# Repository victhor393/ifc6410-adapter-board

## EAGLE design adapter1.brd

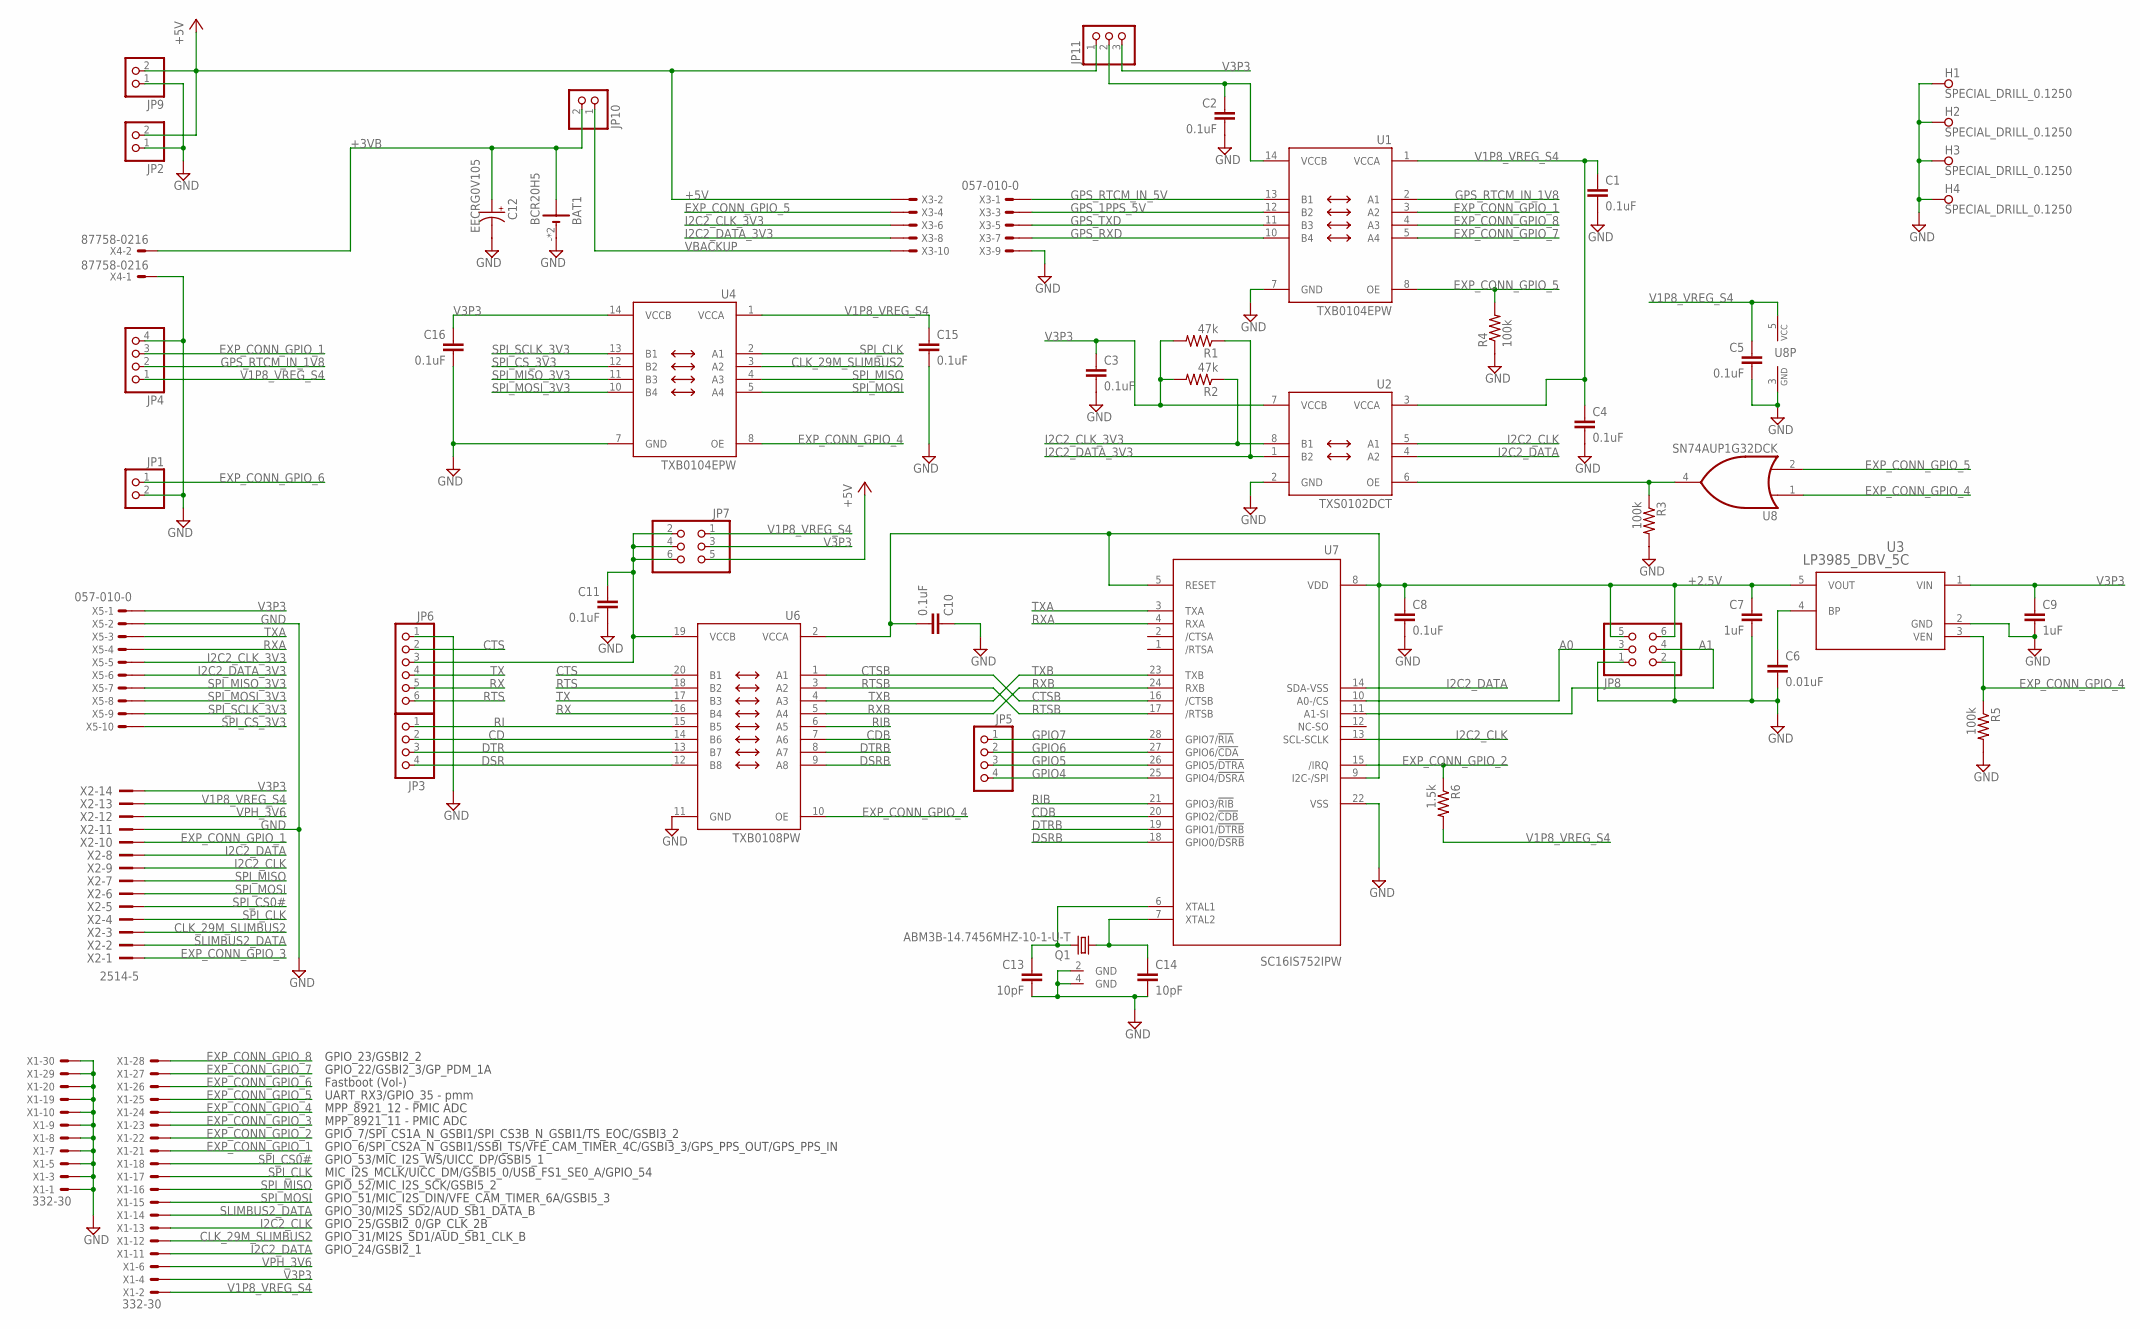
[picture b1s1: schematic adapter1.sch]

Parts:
BAT1: BCR20H5; BCR20H5_1066
C1, C2, C3, C4, C5, C8, C10, C11, C15, C16: 0.1uF; C0603
C6: 0.01uF; C0603
C7, C9: 1uF; C0603
C12: EECRG0V105; EB20D
C13, C14: 10pF; C0603
H1, H2, H3, H4: SPECIAL_DRILL_0.1250; PAD_0.1250
JP1, JP2, JP9: PINHD-1X2/90; 1X02/90
JP3, JP4, JP5: PINHD-1X4/90; 1X04/90
JP6: PINHD-1X6/90; 1X06/90
JP7: PINHD-2X3/90; 2X03/90
JP8: PINHD-2X3; 2X03
JP10: PINHD-1X2; 1X02
JP11: PINHD-1X3; 1X03
Q1: ABM3B-14.7456MHZ-10-1-U-T; ABM3B
R1, R2: 47k; R0603
R3, R4, R5: 100k; R0603
R6: 1.5k; R0603
U1, U4: TXB0104EPW; PW_R-PDSO-G14
U2: TXS0102DCT; DCT_R-PDSO-G8
U3: LP3985_DBV_5C; MF05A-M
U6: TXB0108PW; PW_R-PDSO-G20
U7: SC16IS752IPW; SSOP28
U8: SN74AUP1G32DCK; SC70-5
X1: 332-30
X2: 2514-5; PAK100/2500-5-14
X3, X5: 057-010-0
X4: 87758-0216

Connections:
+2.5V: C7.1, C8.1, C10.2, JP8.5, JP8.6, U3.5 (VOUT), U6.2 (VCCA), U7.5 (RESET), U7.8 (VDD), U7.9 (I2C-/SPI)
+3VB: BAT1.+, BAT1.+1 (+), C12.+, JP10.2, X4.2
+5V: JP2.2, JP7.5, JP9.2, JP11.1, X3.2
A0: JP8.3, U7.10 (A0-/CS)
A1: JP8.4, U7.11 (A1-SI)
CD: JP3.2, U6.14 (B6)
CDB: U6.7 (A6), U7.20 (GPIO2/!CDB)
CLK_29M_SLIMBUS2: U4.3 (A2), X1.12, X2.3
CTS: JP6.2, U6.20 (B1)
CTSB: U6.1 (A1), U7.16 (/CTSB)
DSR: JP3.4, U6.12 (B8)
DSRB: U6.9 (A8), U7.18 (GPIO0/!DSRB)
DTR: JP3.3, U6.13 (B7)
DTRB: U6.8 (A7), U7.19 (GPIO1/!DTRB)
EXP_CONN_GPIO_1: JP4.3, U1.3 (A2), X1.21, X2.10
EXP_CONN_GPIO_2: R6.1, U7.15 (/IRQ), X1.22
EXP_CONN_GPIO_3: X1.23, X2.1
EXP_CONN_GPIO_4: R5.1, U3.3 (VEN), U4.8 (OE), U6.10 (OE), U8.1 (I0), X1.24
EXP_CONN_GPIO_5: R4.2, U1.8 (OE), U8.2 (I1), X1.25, X3.4
EXP_CONN_GPIO_6: JP1.1, X1.26
EXP_CONN_GPIO_7: U1.5 (A4), X1.27
EXP_CONN_GPIO_8: U1.4 (A3), X1.28
GND: BAT1.-, BAT1.-1 (-), C1.2, C2.2, C3.2, C4.2, C5.2, C6.2, C7.2, C8.2, C9.2, C10.1, C11.2, C12.-, C13.2, C14.2, C15.2, C16.2, H1.1, H2.1, H3.1, H4.1, JP1.2, JP2.1, JP4.4, JP6.1, JP8.1, JP8.2, JP9.1, Q1.2 (GND), Q1.4 (GND), R3.2, R4.1, R5.2, U1.7 (GND), U2.2 (GND), U3.2 (GND), U4.7 (GND), U6.11 (GND), U7.22 (VSS), U8.3 (GND), X1.1, X1.3, X1.5, X1.7, X1.8, X1.9, X1.10, X1.19, X1.20, X1.29, X1.30, X2.11, X3.9, X4.1, X5.2
GPIO4: JP5.4, U7.25 (GPIO4/!DSRA)
GPIO5: JP5.3, U7.26 (GPIO5/!DTRA)
GPIO6: JP5.2, U7.27 (GPIO6/!CDA)
GPIO7: JP5.1, U7.28 (GPIO7/!RIA)
GPS_1PPS_5V: U1.12 (B2), X3.3
GPS_RTCM_IN_1V8: JP4.2, U1.2 (A1)
GPS_RTCM_IN_5V: U1.13 (B1), X3.1
GPS_RXD: U1.10 (B4), X3.7
GPS_TXD: U1.11 (B3), X3.5
I2C2_CLK: U2.5 (A1), U7.13 (SCL-SCLK), X1.13, X2.9
I2C2_CLK_3V3: R2.1, U2.8 (B1), X3.6, X5.5
I2C2_DATA: U2.4 (A2), U7.14 (SDA-VSS), X1.11, X2.8
I2C2_DATA_3V3: R1.1, U2.1 (B2), X3.8, X5.6
unnamed: C2.1, JP11.2, U1.14 (VCCB)
unnamed: C14.1, Q1.3 (2), U7.7 (XTAL2)
unnamed: C13.1, Q1.1, U7.6 (XTAL1)
unnamed: C11.1, JP6.3, JP7.2, JP7.4, JP7.6, U6.19 (VCCB)
unnamed: C6.1, U3.4 (BP)
unnamed: R3.1, U2.6 (OE), U8.4 (O)
RI: JP3.1, U6.15 (B5)
RIB: U6.6 (A5), U7.21 (GPIO3/!RIB)
RTS: JP6.6, U6.18 (B2)
RTSB: U6.3 (A2), U7.17 (/RTSB)
RX: JP6.5, U6.16 (B4)
RXA: U7.4 (RXA), X5.4
RXB: U6.5 (A4), U7.24 (RXB)
SLIMBUS2_DATA: X1.14, X2.2
SPI_CLK: U4.2 (A1), X1.17, X2.4
SPI_CS0#: X1.18, X2.5
SPI_CS_3V3: U4.12 (B2), X5.10
SPI_MISO: U4.4 (A3), X1.16, X2.7
SPI_MISO_3V3: U4.11 (B3), X5.7
SPI_MOSI: U4.5 (A4), X1.15, X2.6
SPI_MOSI_3V3: U4.10 (B4), X5.8
SPI_SCLK_3V3: U4.13 (B1), X5.9
TX: JP6.4, U6.17 (B3)
TXA: U7.3 (TXA), X5.3
TXB: U6.4 (A3), U7.23 (TXB)
V1P8_VREG_S4: C1.1, C4.1, C5.1, C15.1, JP4.1, JP7.1, R6.2, U1.1 (VCCA), U2.3 (VCCA), U4.1 (VCCA), U8.5 (VCC), X1.2, X2.13
V3P3: C3.1, C9.1, C16.1, JP7.3, JP11.3, R1.2, R2.2, U2.7 (VCCB), U3.1 (VIN), U4.14 (VCCB), X1.4, X2.14, X5.1
VBACKUP: JP10.1, X3.10
VPH_3V6: X1.6, X2.12

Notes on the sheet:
GPIO_51/MIC_I2S_DIN/VFE_CAM_TIMER_6A/GSBI5_3
GPIO_52/MIC_I2S_SCK/GSBI5_2
GPIO_53/MIC_I2S_WS/UICC_DP/GSBI5_1
MIC_I2S_MCLK/UICC_DM/GSBI5_0/USB_FS1_SE0_A/GPIO_54
GPIO_30/MI2S_SD2/AUD_SB1_DATA_B
GPIO_25/GSBI2_0/GP_CLK_2B
GPIO_31/MI2S_SD1/AUD_SB1_CLK_B
GPIO_24/GSBI2_1
GPIO_6/SPI_CS2A_N_GSBI1/SSBI_TS/VFE_CAM_TIMER_4C/GSBI3_3/GPS_PPS_OUT/GPS_PPS_IN
GPIO_7/SPI_CS1A_N_GSBI1/SPI_CS3B_N_GSBI1/TS_EOC/GSBI3_2
MPP_8921_11 - PMIC ADC
MPP_8921_12 - PMIC ADC
UART_RX3/GPIO_35 - pmm
Fastboot (Vol-)
GPIO_23/GSBI2_2
GPIO_22/GSBI2_3/GP_PDM_1A

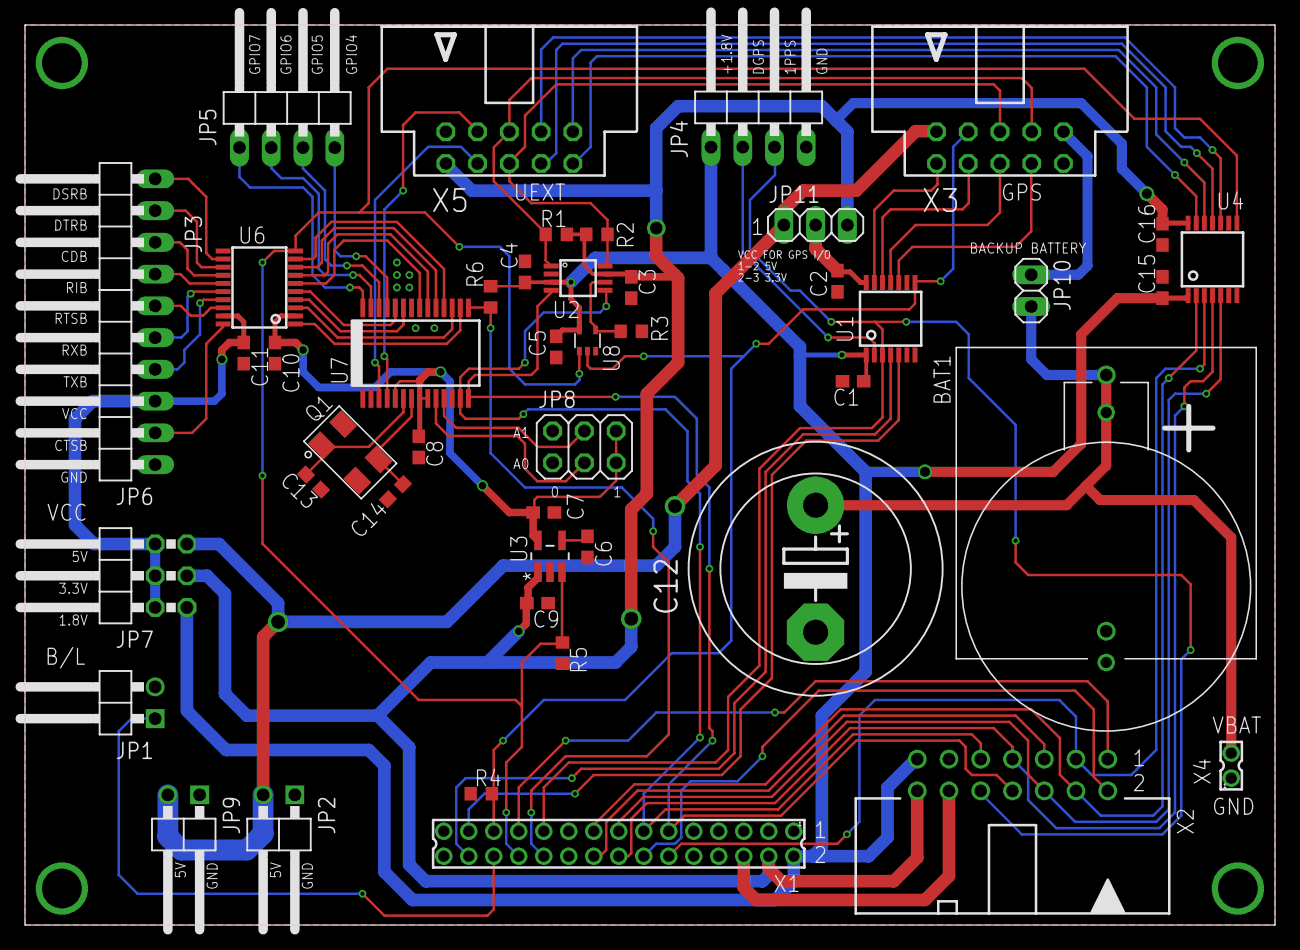
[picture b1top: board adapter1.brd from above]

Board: 2 copper layers, 100.0 x 72.0 mm, 51 parts (0 on the bottom side), 65 nets.

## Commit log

2019-05-21 Added schematic and board layout in pdf format
